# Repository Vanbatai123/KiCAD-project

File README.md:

# KiCAD-project
a repo to store KiCAD project

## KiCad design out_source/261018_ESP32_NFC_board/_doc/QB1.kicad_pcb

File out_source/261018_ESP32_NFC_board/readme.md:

Summary
Hi there,

I have a nearly-complete 4-layer KiCad 7 PCB (55×55mm, ESP32-S3 + NFC + USB-C). An AI autorouter finished ~90% of the routing. I need a human to do the final cleanup before fab.
What needs to be done:

Fix 13 DRC clearance violations (grid-resolution artifacts, no rerouting needed — just nudge)
Route 4 remaining connections (CC1, BOOT, redundant USB-C D+ contact)
Confirm GND plane L2 and 3V3 plane L3 are filled correctly
DRC to zero errors
Export Gerbers + drill file for JLCPCB (4-layer)

I provide:

.kicad_pcb with all components placed and 35/39 nets routed
.kicad_sch schematic
Custom footprint library (fp_lib/)
DRC status report listing every issue with location and suggested fix

Requirements:

KiCad 7 (not older)
Experience with 4-layer EMC-conscious boards
Deliver: fixed .kicad_pcb + Gerbers ZIP ready for JLCPCB

I am not a PCB designer myself and I cannot evaluate the AI's work. If you open the files and find issues beyond the DRC report — wrong footprints, bad routing decisions, schematic errors, anything that would cause problems at fab or in the field — please tell me before fixing anything. I'd rather know and discuss than get a clean DRC with hidden problems.

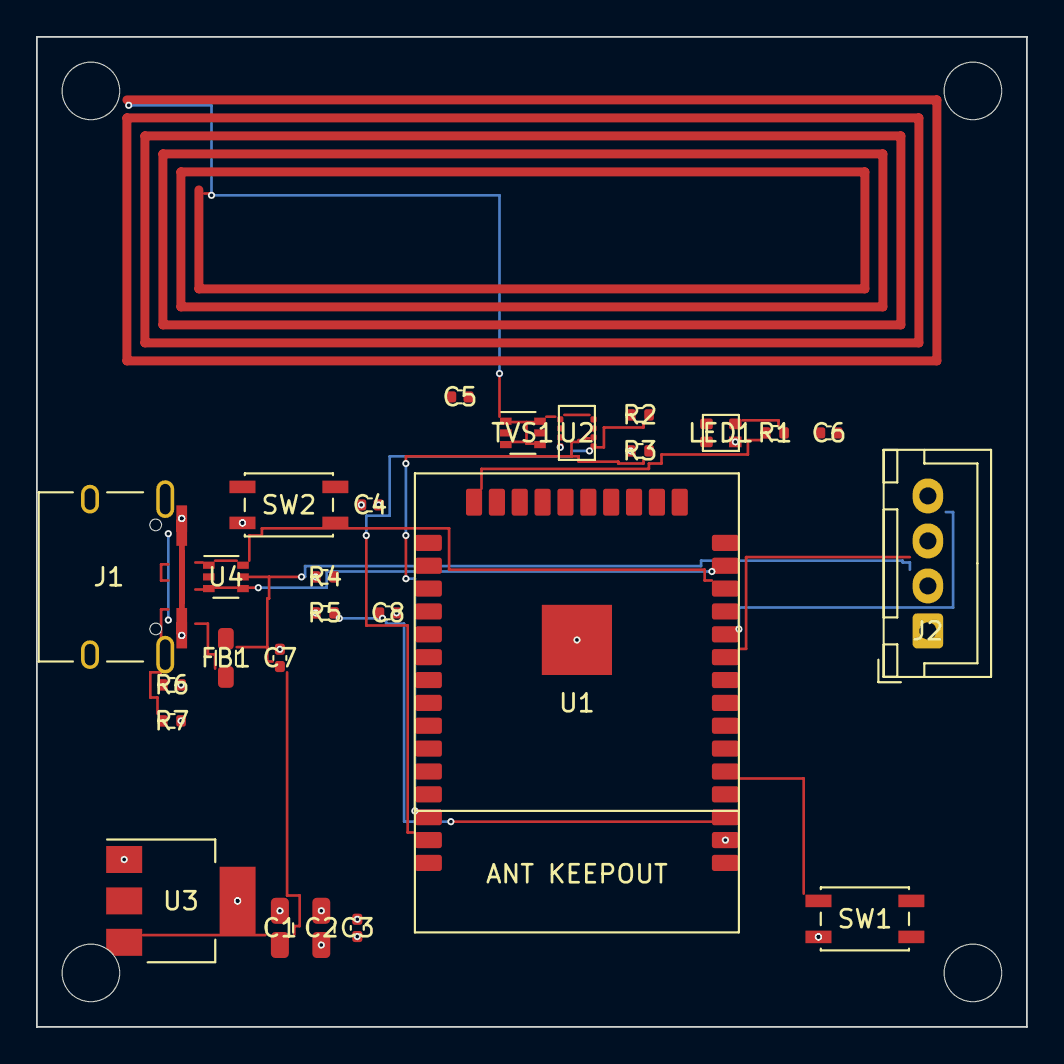
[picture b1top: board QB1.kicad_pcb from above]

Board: 4 copper layers, 55.0 x 55.0 mm, 26 parts (0 on the bottom side), 18 nets.

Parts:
C1, C2: 10uF; C_0805_2012Metric
C3: 1uF; C_0402_1005Metric
C4, C5, C6, C7, C8: 100nF; C_0402_1005Metric
FB1: 600R@100MHz; L_0805_2012Metric
J1: USB-C-16P; USB_C_Receptacle_HRO_TYPE-C-31-M-12
J2: B4B-XH-A; JST_XH_B4B-XH-A_1x04_P2.50mm_Vertical
LED1: WS2812B-2020; LED_2020
R1: 33R; R_0402_1005Metric
R2, R3: 4.7k; R_0402_1005Metric
R4, R5: 10k; R_0402_1005Metric
R6, R7: 5.1k; R_0402_1005Metric
SW1, SW2: TS-1187A; SW_SPST_EVQP2
TVS1: PRTR5V0U2X; SOT-363_SC-70-6
U1: ESP32-S3-WROOM-1-N8; ESP32-S3-WROOM-1
U2: ST25DV16K-JF; UFPGA-8_2x3mm_P0.5mm
U3: AMS1117-3.3; SOT-223-3_TabPin2
U4: USBLC6-2SC6; SOT-363_SC-70-6

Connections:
BOOT: R4.2, SW2.1, U1.27
CC1: J1.A5, R6.1
CC2: J1.B5, R7.1
EN: C8.1, R5.2, U1.3
GND: C1.2, C2.2, C3.2, C4.2, C5.2, C6.2, C7.2, C8.2, J1.A1, J1.A12, J1.B1, J1.B12, J1.S1, J2.1, LED1.2, R6.2, R7.2, SW1.2, SW2.2, TVS1.2, TVS1.5, U1.1, U1.40, U1.41, U2.3, U3.1, U4.2
I2C_SCL: R3.2, U1.38, U2.6
I2C_SDA: R2.2, U1.39, U2.5
LED_DATA: R1.1, U1.25
LED_DIN: LED1.3, R1.2
NFC_ANT: TVS1.1, TVS1.3, TVS1.4, TVS1.6, U2.1, U2.8
PRN_RX: J2.4, U1.11
PRN_TX: J2.3, U1.10
SW_PRINT: SW1.1, U1.5
USB_DM: J1.A7, J1.B7, U1.13, U4.1, U4.6
USB_DP: J1.A6, J1.B6, U1.14, U4.3, U4.4
VBUS: FB1.1, J1.A4, J1.A9, J1.B4, J1.B9
VCC3V3: C2.1, C3.1, C4.1, C5.1, C6.1, LED1.4, R2.1, R3.1, R4.1, R5.1, U1.2, U2.4, U3.2
VIN_FILT: C1.1, C7.1, FB1.2, J2.2, U3.3, U4.5

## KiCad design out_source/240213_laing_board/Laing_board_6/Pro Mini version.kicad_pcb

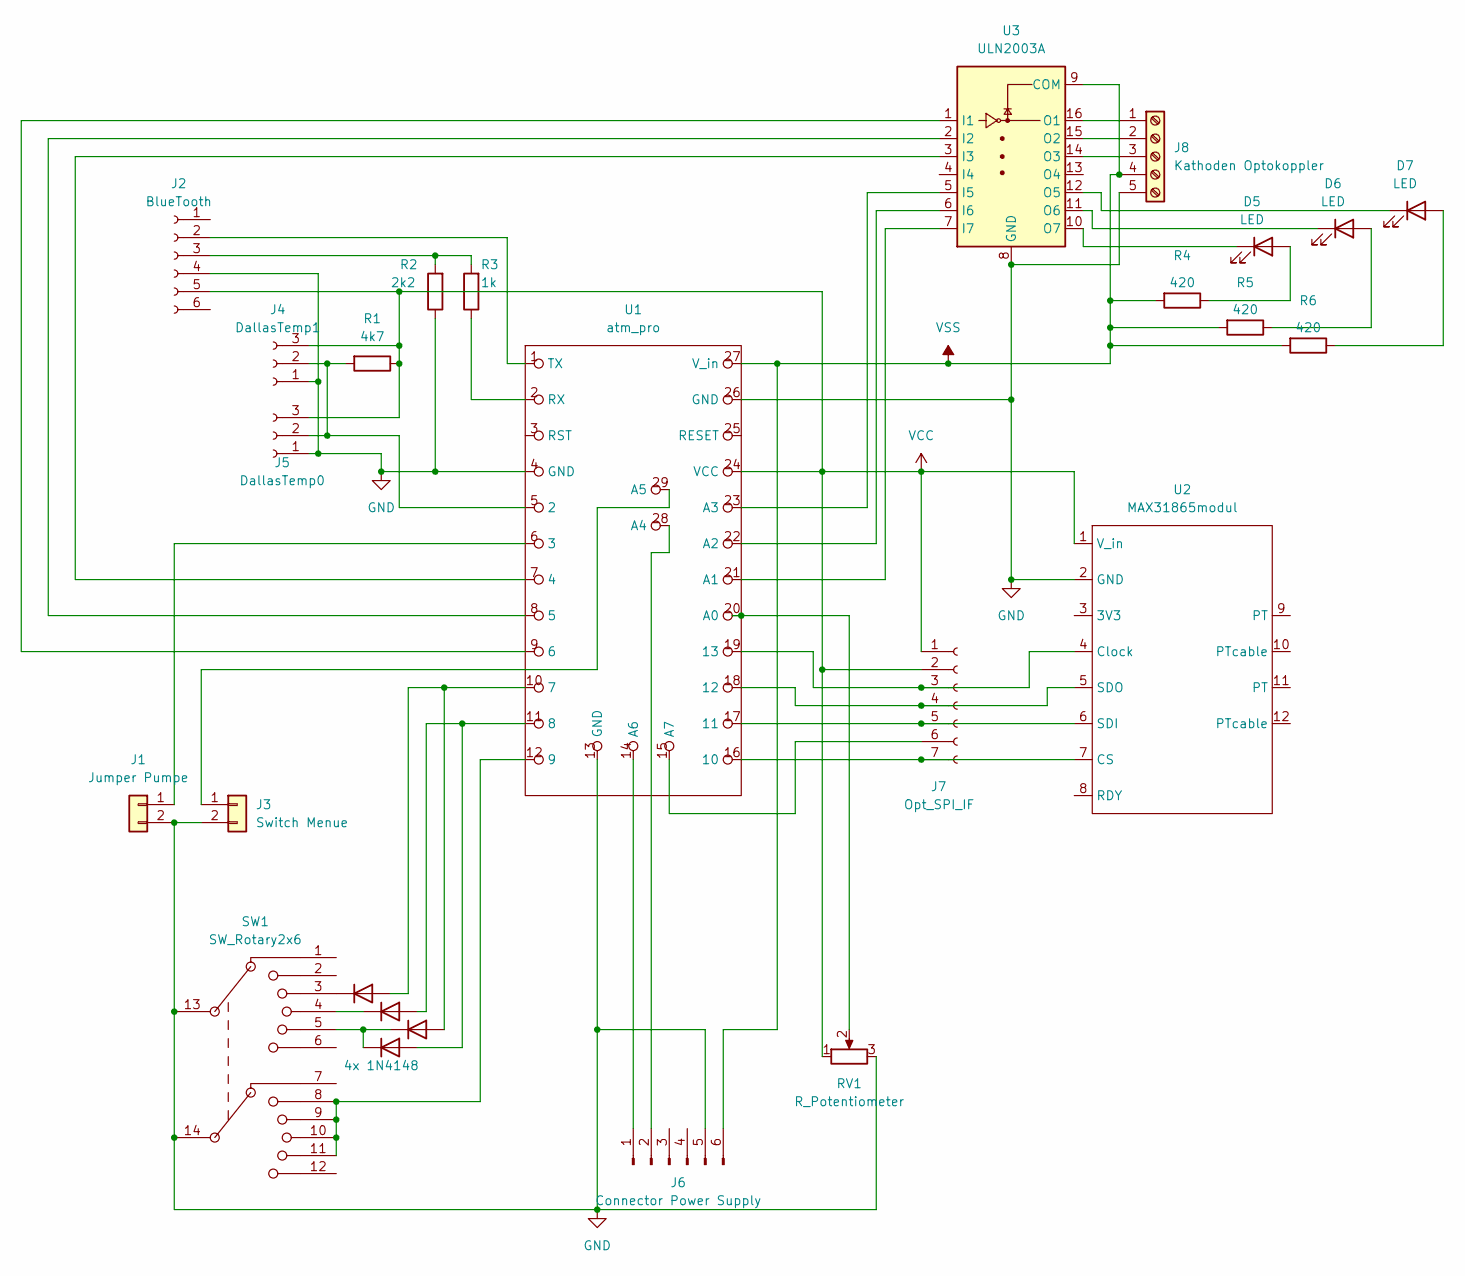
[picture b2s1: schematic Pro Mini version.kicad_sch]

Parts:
D1: 4x 1N4148; D_0201_0603Metric_Pad0.64x0.40mm_HandSolder
D2, D3, D4: 1N4148; D_0201_0603Metric_Pad0.64x0.40mm_HandSolder
D5, D6, D7: LED; LED_1812_4532Metric_Pad1.30x3.40mm_HandSolder
J1: Jumper Pumpe; PinHeader_1x02_P2.54mm_Vertical
J2: BlueTooth; PinHeader_1x06_P2.54mm_Horizontal
J3: Switch Menue; PinHeader_1x02_P2.54mm_Vertical
J4: DallasTemp1; PinHeader_1x03_P2.54mm_Vertical
J5: DallasTemp0; PinHeader_1x03_P2.54mm_Vertical
J6: Connector Power Supply; PhoenixContact_MSTBVA_2,5_6-G-5,08_1x06_P5.08mm_Vertical
J7: Opt_SPI_IF; PinSocket_1x07_P2.54mm_Vertical
J8: Kathoden Optokoppler; KF141R-2.54-5P
R1: 4k7; R_0815_2038Metric_Pad1.20x4.05mm_HandSolder
R2: 2k2; R_0815_2038Metric_Pad1.20x4.05mm_HandSolder
R3: 1k; R_0815_2038Metric_Pad1.20x4.05mm_HandSolder
R4, R5, R6: 420; R_0815_2038Metric_Pad1.20x4.05mm_HandSolder
RV1: R_Potentiometer; Potentiometer_Bourns_3314R-1_Vertical_Hole
SW1: SW_Rotary2x6; sw_2x6
U1: atm_pro; ATM_PRO
U2: MAX31865modul; PinHeader_1x08_P2.54mm_Vertical
U3: ULN2003A; DIP-16_W7.62mm

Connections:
GND: J1.2, J2.4, J3.2, J4.1, J5.1, J6.5, J8.5, R2.1, RV1.3, SW1.13, SW1.14, U1.4 (GND), U1.13 (GND), U1.26 (GND), U2.2 (GND), U3.8 (GND)
unnamed: D1.1 (K), SW1.3
unnamed: D1.2 (A), D2.2 (A), U1.10 (7)
unnamed: D2.1 (K), D4.1 (K), SW1.5
unnamed: D3.1 (K), SW1.4
unnamed: D3.2 (A), D4.2 (A), U1.11 (8)
unnamed: D5.1 (K), U3.10 (O7)
unnamed: D5.2 (A), R4.1
unnamed: D6.1 (K), U3.11 (O6)
unnamed: D6.2 (A), R5.1
unnamed: D7.1 (K), U3.12 (O5)
unnamed: D7.2 (A), R6.1
unnamed: J1.1, U1.6 (3)
unnamed: J2.2, U1.1 (TX)
unnamed: J2.3, R2.2, R3.2
unnamed: J3.1, U1.29 (A5)
unnamed: J4.2, J5.2, R1.2, U1.5 (2)
unnamed: J6.1, U1.14 (A6)
unnamed: J6.2, U1.28 (A4)
unnamed: J7.3, U1.19 (13), U2.4 (Clock)
unnamed: J7.4, U1.18 (12), U2.5 (SDO)
unnamed: J7.5, U1.17 (11), U2.6 (SDI)
unnamed: J7.6, U1.15 (A7)
unnamed: J7.7, U1.16 (10), U2.7 (CS)
unnamed: J8.1, U3.16 (O1)
unnamed: J8.2, U3.15 (O2)
unnamed: J8.3, U3.14 (O3)
unnamed: R3.1, U1.2 (RX)
unnamed: RV1.2, U1.20 (A0)
unnamed: SW1.8, SW1.9, SW1.10, SW1.11, U1.12 (9)
unnamed: U1.7 (4), U3.3 (I3)
unnamed: U1.8 (5), U3.2 (I2)
unnamed: U1.9 (6), U3.1 (I1)
unnamed: U1.21 (A1), U3.7 (I7)
unnamed: U1.22 (A2), U3.6 (I6)
unnamed: U1.23 (A3), U3.5 (I5)
VCC: J2.5, J4.3, J5.3, J7.1, J7.2, R1.1, RV1.1, U1.24 (VCC), U2.1 (V_in)
VSS: J6.6, J8.4, R4.2, R5.2, R6.2, U1.27 (V_in), U3.9 (COM)

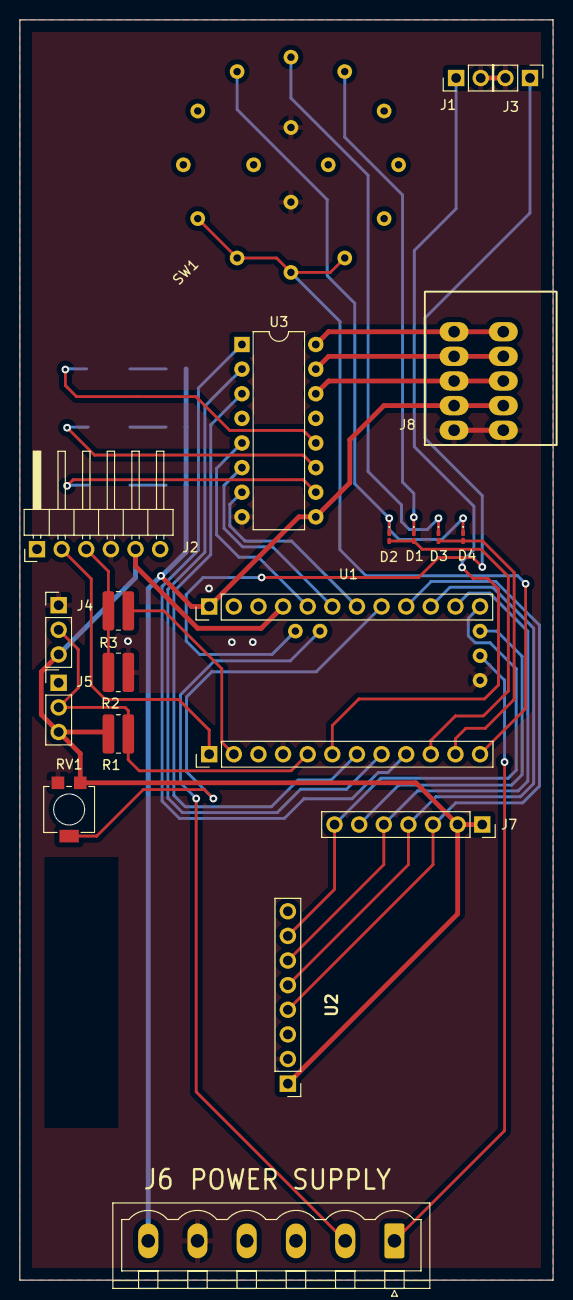
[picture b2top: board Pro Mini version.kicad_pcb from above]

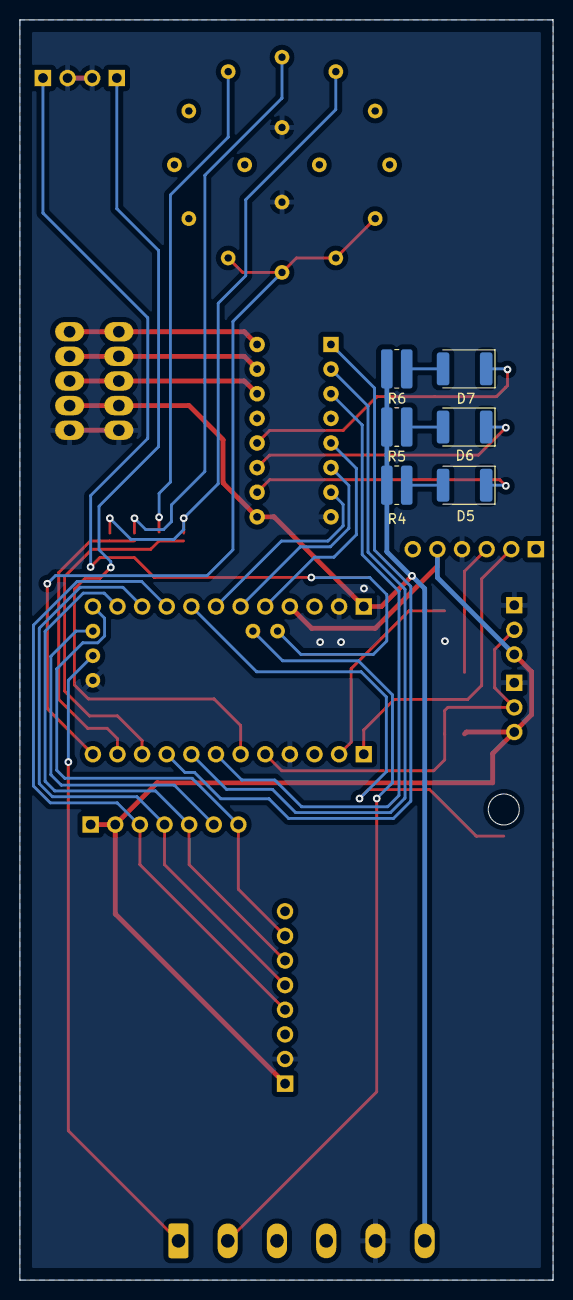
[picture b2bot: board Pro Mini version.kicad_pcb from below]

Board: 2 copper layers, 55.0 x 130.0 mm, 26 parts (6 on the bottom side), 38 nets.
